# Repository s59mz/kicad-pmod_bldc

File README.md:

# kicad-pmod_bldc
PMOD PCB module with DRV10983 device for driving a Brush Less DC (bldc) Motor 

Schematic:
[kicad-pmod_bldc.pdf](kicad-pmod_bldc.pdf)

BOM:
[kicad-pmod_bldc.csv](kicad-pmod_bldc.csv)

Pick&Place:
[kicad-pmod_bldc_pos.csv](kicad-pmod_bldc_pos.csv)

Gerbers:
[gerbers.zip](https://github.com/s59mz/kicad-pmod_bldc/raw/main/gerbers.zip)

Related Tutorial:
[Hackster - Adam Taylor](https://www.hackster.io/adam-taylor/zuboard-petalinux-motor-control-3eee98)

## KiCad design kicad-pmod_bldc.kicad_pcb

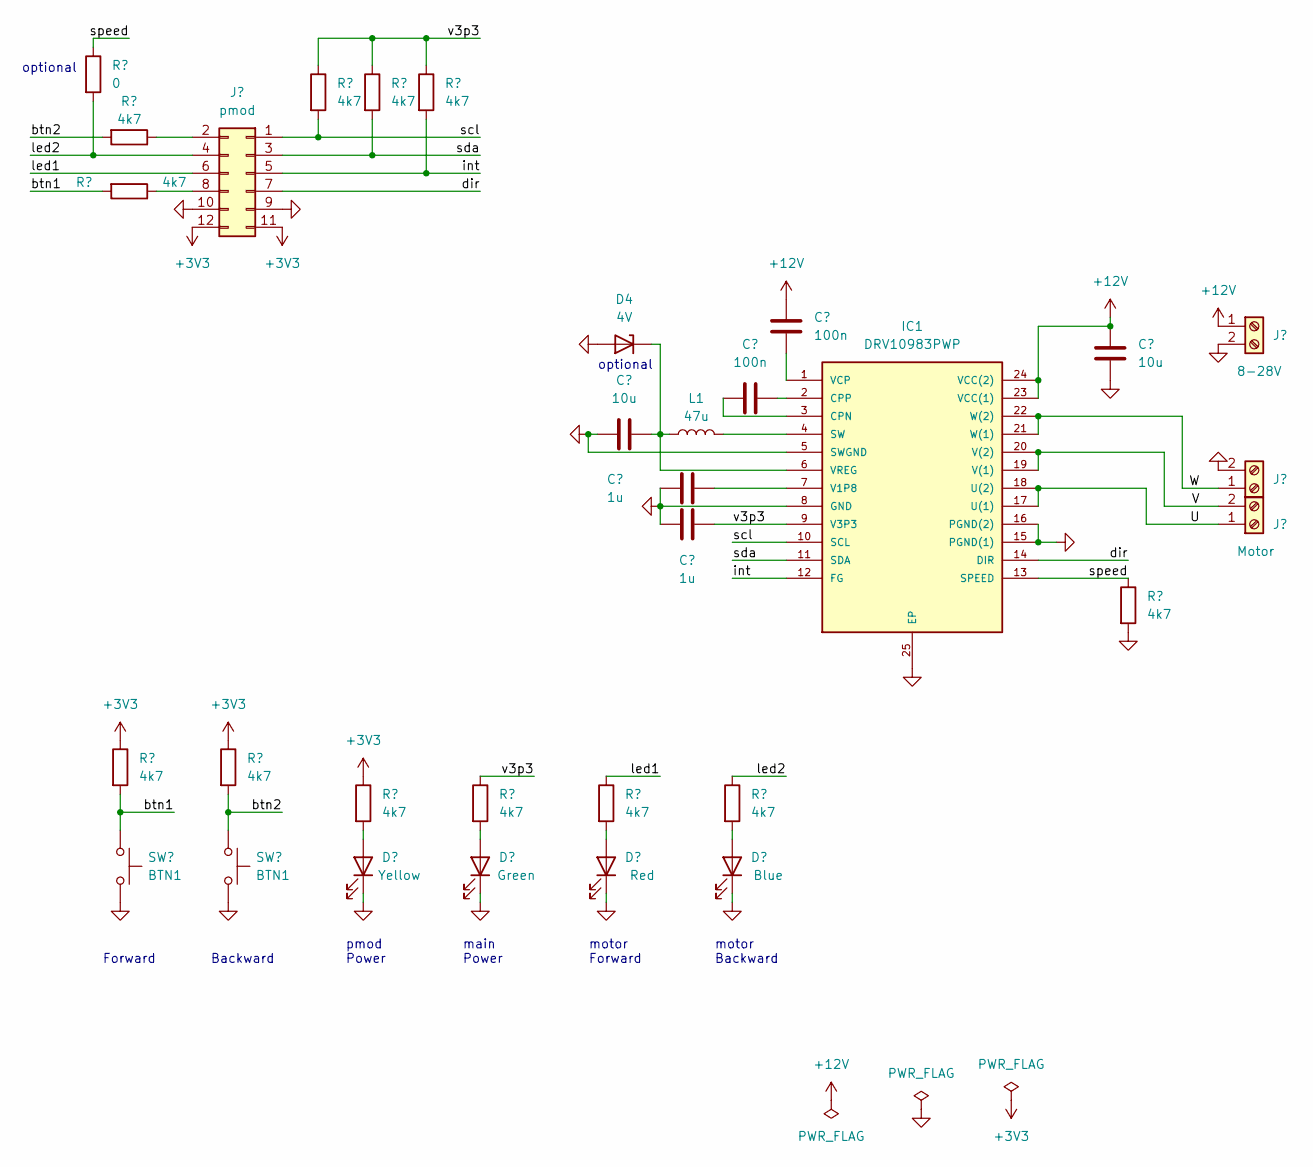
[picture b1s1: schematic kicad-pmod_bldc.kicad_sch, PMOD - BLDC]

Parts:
C1, C3: 100n; C_0603_1608Metric_Pad1.08x0.95mm_HandSolder
C2: 10u; C_1210_3225Metric_Pad1.33x2.70mm_HandSolder
C4: 10u; C_0603_1608Metric_Pad1.08x0.95mm_HandSolder
C5, C6: 1u; C_0603_1608Metric_Pad1.08x0.95mm_HandSolder
D1: Red; LED_0603_1608Metric_Pad1.05x0.95mm_HandSolder
D2: Blue; LED_0603_1608Metric_Pad1.05x0.95mm_HandSolder
D3: Green; LED_0603_1608Metric_Pad1.05x0.95mm_HandSolder
D4: 4V; D_0603_1608Metric_Pad1.05x0.95mm_HandSolder
D5: Yellow; LED_0603_1608Metric_Pad1.05x0.95mm_HandSolder
IC1: DRV10983PWP; HTSSOP-24-1EP_4.4x7.8mm_P0.65mm_EP3.4x7.8mm_Mask2.4x4.68mm_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; MANUFACTURER_PART_NUMBER DRV10983PWP; LCSC C115806
J1: pmod; PinHeader_2x06_P2.54mm_Horizontal; LCSC C2911299
J2: 8-28V; TerminalBlock_bornier-2_P5.08mm; LCSC C474952
J3: motor; TerminalBlock_bornier-2_P5.08mm; LCSC C474952
J4: Motor; TerminalBlock_bornier-2_P5.08mm; LCSC C474952
L1: 47u; L_0603_1608Metric_Pad1.05x0.95mm_HandSolder
R1: 0; R_0603_1608Metric_Pad0.98x0.95mm_HandSolder
R2, R3, R4, R5, R6, R7, R8, R9, R10, R11, R12, R13: 4k7; R_0603_1608Metric_Pad0.98x0.95mm_HandSolder
SW1, SW2: BTN1; SW_SPST_CK_RS282G05A3; LCSC C255802

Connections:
+3V3: J1.11, J1.12, R8.1, R9.1, R10.1
+12V: C1.1, C2.1, IC1.23 (VCC(1)), IC1.24 (VCC(2)), J2.1
/U: IC1.17 (U(1)), IC1.18 (U(2)), J4.1
/V: IC1.19 (V(1)), IC1.20 (V(2)), J4.2
/W: IC1.21 (W(1)), IC1.22 (W(2)), J3.1
/btn1: R6.2, R8.2, SW1.1
/btn2: R5.2, R9.2, SW2.1
/dir: IC1.14 (DIR), J1.7
/int: IC1.12 (FG), J1.5, R4.2
/led1: J1.6, R12.1
/led2: J1.4, R1.2, R13.1
/scl: IC1.10 (SCL), J1.1, R2.2
/sda: IC1.11 (SDA), J1.3, R3.2
/speed: IC1.13 (SPEED), R1.1, R7.1
/v3p3: C6.2, IC1.9 (V3P3), R2.1, R3.1, R4.1, R11.1
GND: C2.2, C4.1, C5.1, C6.1, D1.1 (K), D2.1 (K), D3.1 (K), D4.2 (A), D5.1 (K), IC1.5 (SWGND), IC1.8 (GND), IC1.15 (PGND(1)), IC1.16 (PGND(2)), IC1.25 (EP), J1.9, J1.10, J2.2, J3.2, R7.2, SW1.2, SW2.2
unnamed: D1.2 (A), R12.2
unnamed: D2.2 (A), R13.2
unnamed: D3.2 (A), R11.2
unnamed: C4.2, D4.1 (K), IC1.6 (VREG), L1.1
unnamed: D5.2 (A), R10.2
unnamed: C3.1, IC1.3 (CPN)
unnamed: C3.2, IC1.2 (CPP)
unnamed: IC1.4 (SW), L1.2
unnamed: C5.2, IC1.7 (V1P8)
unnamed: C1.2, IC1.1 (VCP)
unnamed: J1.2, R5.1
unnamed: J1.8, R6.1

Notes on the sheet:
optional
main Power
Backward
pmod Power
Forward
motor Backward
motor Forward

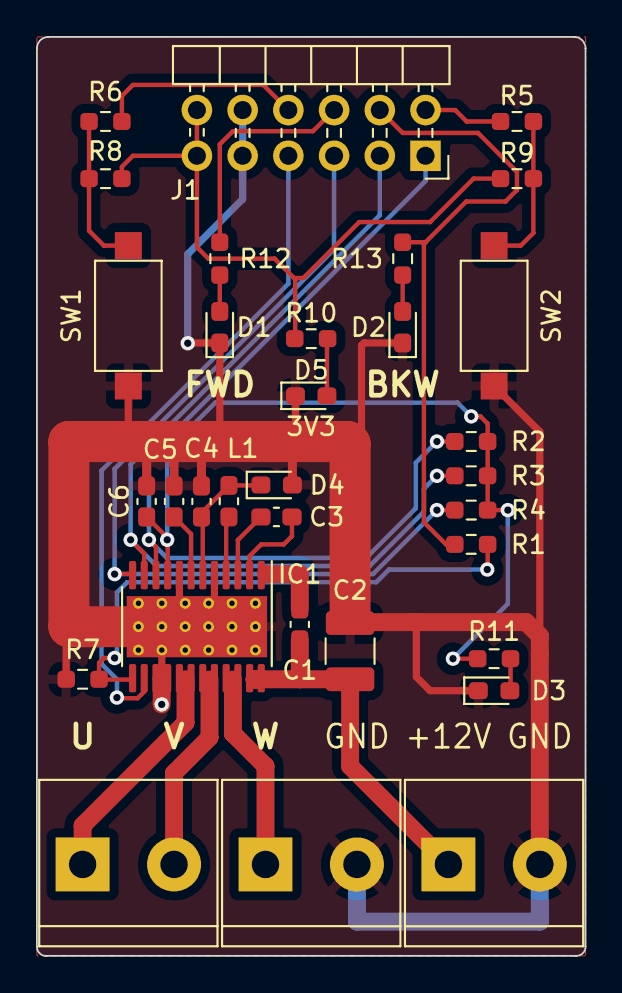
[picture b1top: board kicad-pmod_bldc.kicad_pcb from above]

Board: 2 copper layers, 30.5 x 51.1 mm, 32 parts (0 on the bottom side), 28 nets.

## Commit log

2024-01-17 V1.0
